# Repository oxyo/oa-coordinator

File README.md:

# Open Automation coordinator controller   

This is an Arduino Ethernet compatible device based on [DFRobot Xboard V.2.](http://www.dfrobot.com/index.php?route=product/product&product_id=564) + added Real time clock and radio communication module.
It uses [Ciseco XRF wireless RF radio UART serial data module][] to communicate with Open Automation Center.

This device can collect sensors data over radio channel and retransmit it over network to Open Automation Center or any other web server using HTTP protocol. It can be used to extend Open Automation Center communication range. Also it can be used for the end-point controller purpose, for example to control wireless sockets.  
  
Please check Arduino firmware provided here. Developed on Arduino IDE v.1.05. 
  
For more information please visit [openautomation.center](http://openautomation.center)

Licensed under [WTFPL license terms](http://www.wtfpl.net/)

[Ciseco XRF wireless RF radio UART serial data module]: http://shop.ciseco.co.uk/xrf-wireless-rf-radio-uart-serial-data-module-xbee-shaped/

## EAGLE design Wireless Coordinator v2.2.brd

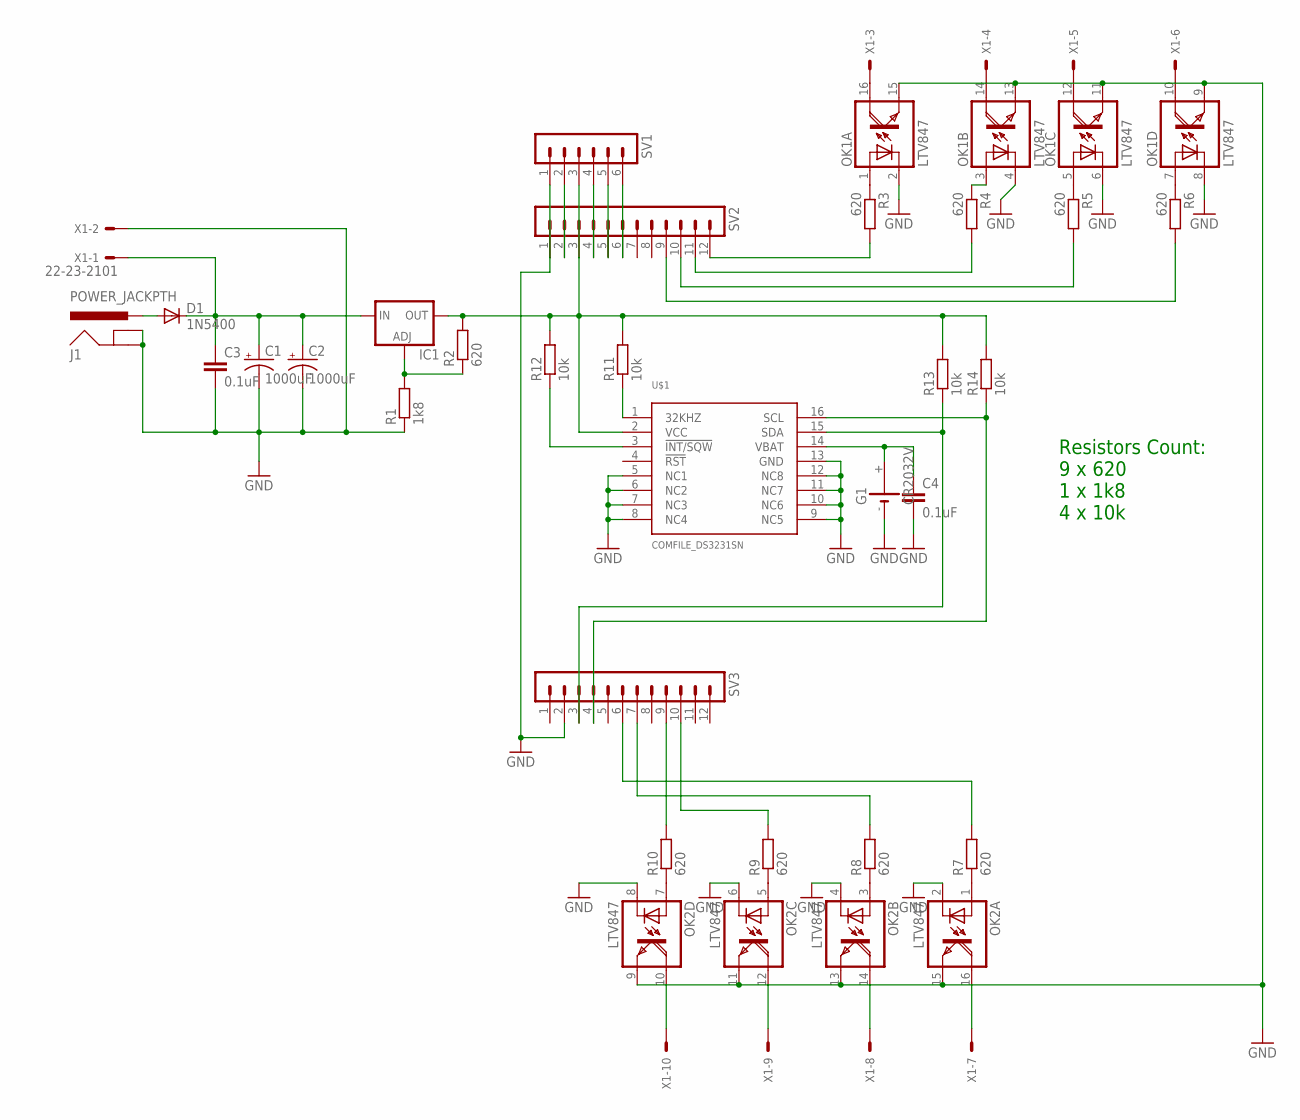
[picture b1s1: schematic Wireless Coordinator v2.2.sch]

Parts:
C1: 1000uF; E5-10,5
C2: 1000uF; E3,5-8
C3, C4: 0.1uF; C050-025X075
D1: 1N5400; DO201-15
G1: CR2032V
IC1: LM317TS; 317TS
J1: POWER_JACKPTH; POWER_JACK_PTH
OK1, OK2: LTV847; DIL16
R1: 1k8; 0207/12
R2, R3, R4, R5, R6, R7, R8, R9, R10: 620; 0207/12
R11, R12, R13, R14: 10k; 0207/12
SV1: MA06-1
SV2, SV3: MA12-1
U$1: COMFILE_DS3231SN; COMFILE_SO16W
X1: 22-23-2101

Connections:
GND: C1.-, C2.-, C3.2, C4.2, G1.-, J1.GND, J1.GNDBREAK, OK1.2 (C), OK1.4 (C), OK1.6 (C), OK1.8 (C), OK1.9 (EMI), OK1.11 (EMI), OK1.13 (EMI), OK1.15 (EMI), OK2.2 (C), OK2.4 (C), OK2.6 (C), OK2.8 (C), OK2.9 (EMI), OK2.11 (EMI), OK2.13 (EMI), OK2.15 (EMI), R1.1, SV1.1, SV2.1, SV3.2, U$1.5 (NC1), U$1.6 (NC2), U$1.7 (NC3), U$1.8 (NC4), U$1.9 (NC5), U$1.10 (NC6), U$1.11 (NC7), U$1.12 (NC8), U$1.13 (GND), X1.2
unnamed: IC1.1 (ADJ), R1.2, R2.1
unnamed: SV1.2, SV2.2
unnamed: IC1.2 (OUT), R2.2, R11.2, R12.2, R13.2, R14.2, SV1.3, SV2.3, U$1.2 (VCC)
unnamed: SV1.4, SV2.4
unnamed: D1.A, J1.PWR
unnamed: SV1.5, SV2.5
unnamed: SV1.6, SV2.6
unnamed: C1.+, C2.+, C3.1, D1.C, IC1.3 (IN), X1.1
unnamed: OK1.1 (A), R3.1
unnamed: OK1.3 (A), R4.1
unnamed: OK1.5 (A), R5.1
unnamed: OK1.7 (A), R6.1
unnamed: OK1.16 (COL), X1.3
unnamed: R4.2, SV2.11
unnamed: OK1.14 (COL), X1.4
unnamed: R6.2, SV2.9
unnamed: OK1.12 (COL), X1.5
unnamed: R5.2, SV2.10
unnamed: OK1.10 (COL), X1.6
unnamed: OK2.1 (A), R7.1
unnamed: R3.2, SV2.12
unnamed: OK2.3 (A), R8.1
unnamed: OK2.5 (A), R9.1
unnamed: OK2.7 (A), R10.1
unnamed: OK2.16 (COL), X1.7
unnamed: OK2.14 (COL), X1.8
unnamed: OK2.12 (COL), X1.9
unnamed: OK2.10 (COL), X1.10
unnamed: R10.2, SV3.9
unnamed: R9.2, SV3.10
unnamed: R8.2, SV3.7
unnamed: R7.2, SV3.6
unnamed: R11.1, U$1.1 (32KHZ)
unnamed: C4.1, G1.+, U$1.14 (VBAT)
unnamed: R12.1, U$1.3 (!INT/SQW)
unnamed: R13.1, SV3.3, U$1.15 (SDA)
unnamed: R14.1, SV3.4, U$1.16 (SCL)

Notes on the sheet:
Resistors Count: 9 x 620 1 x 1k8 4 x 10k

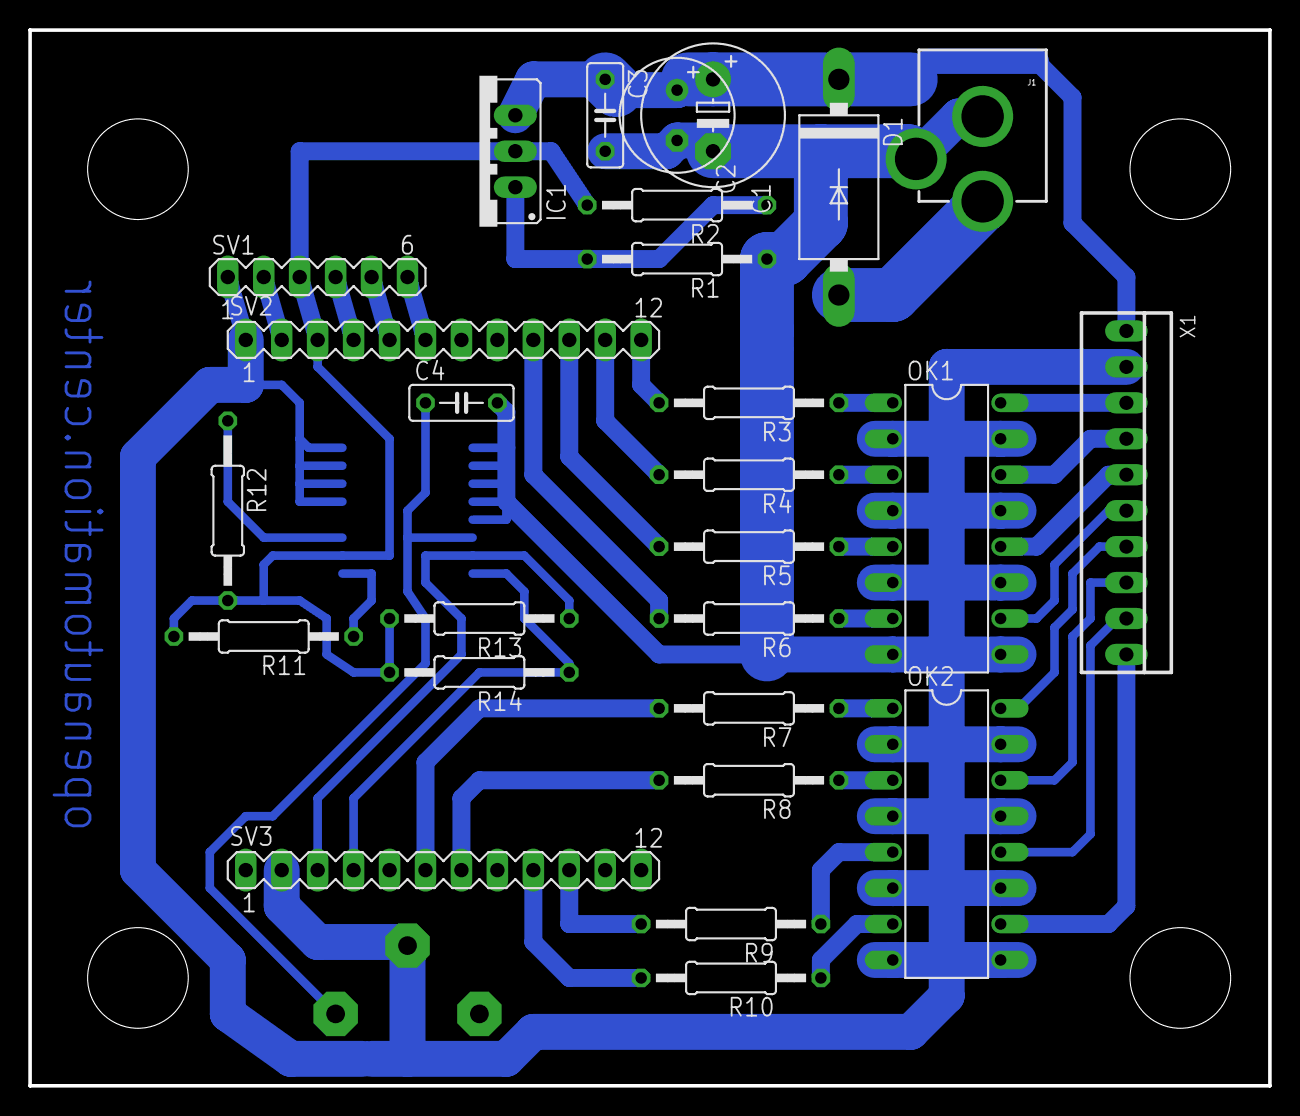
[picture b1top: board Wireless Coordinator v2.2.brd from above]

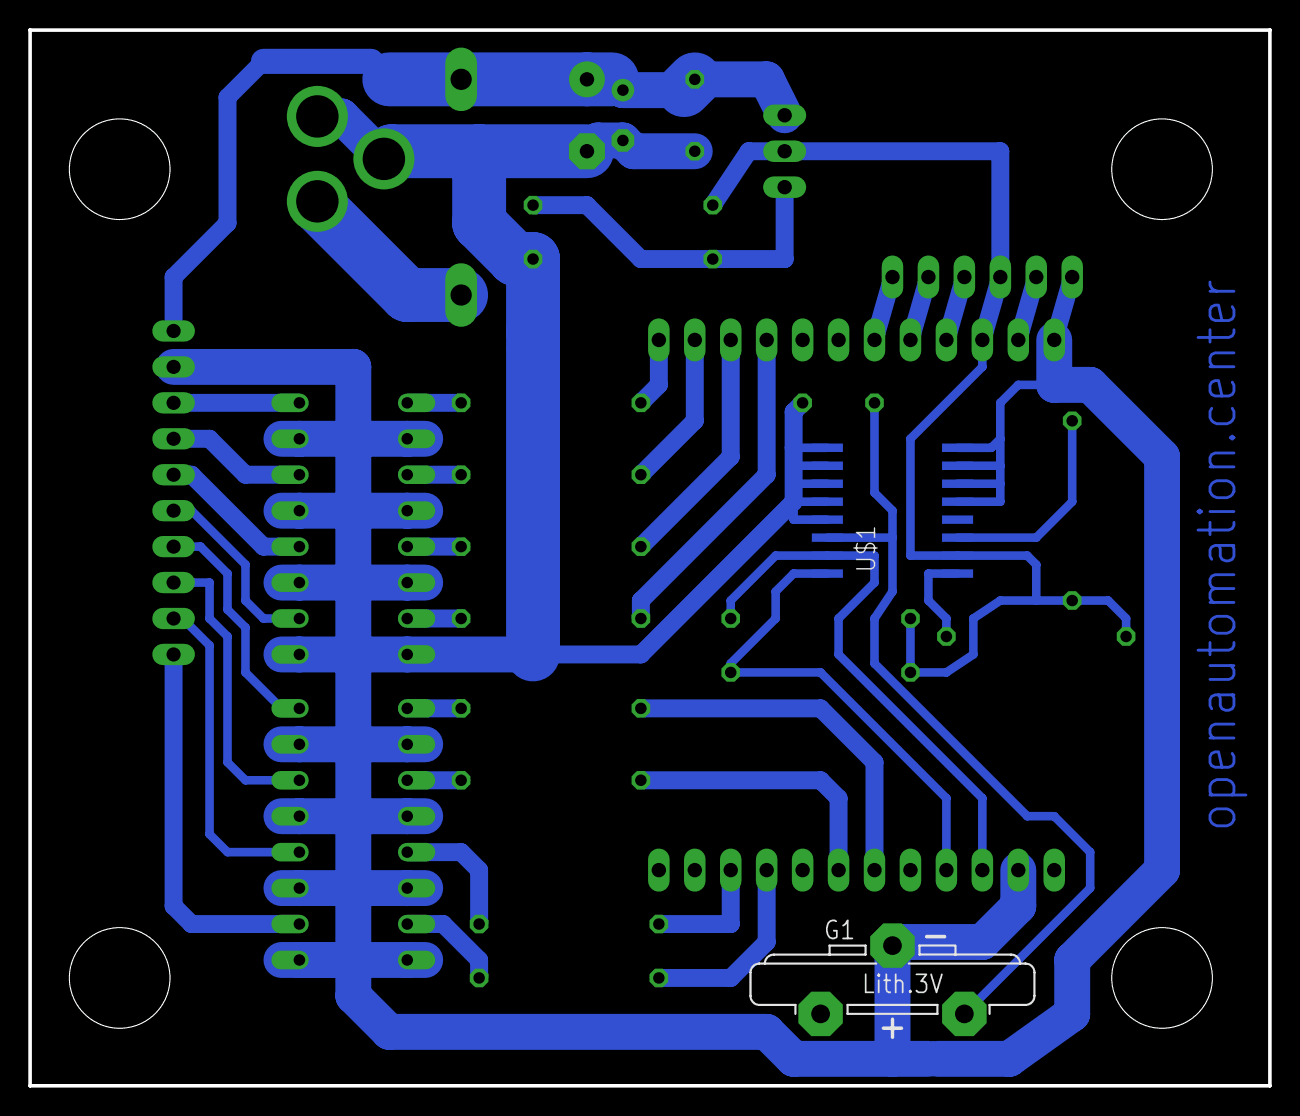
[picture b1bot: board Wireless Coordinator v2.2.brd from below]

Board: 2 copper layers, 87.6 x 74.6 mm, 29 parts (2 on the bottom side), 38 nets.

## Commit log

2015-03-30 Update LICENSE

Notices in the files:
parts and their libraries:
SparkFun-Connectors: Licensing: CC v3.0 Share-Alike You are welcome to use this library for commercial purposes.
